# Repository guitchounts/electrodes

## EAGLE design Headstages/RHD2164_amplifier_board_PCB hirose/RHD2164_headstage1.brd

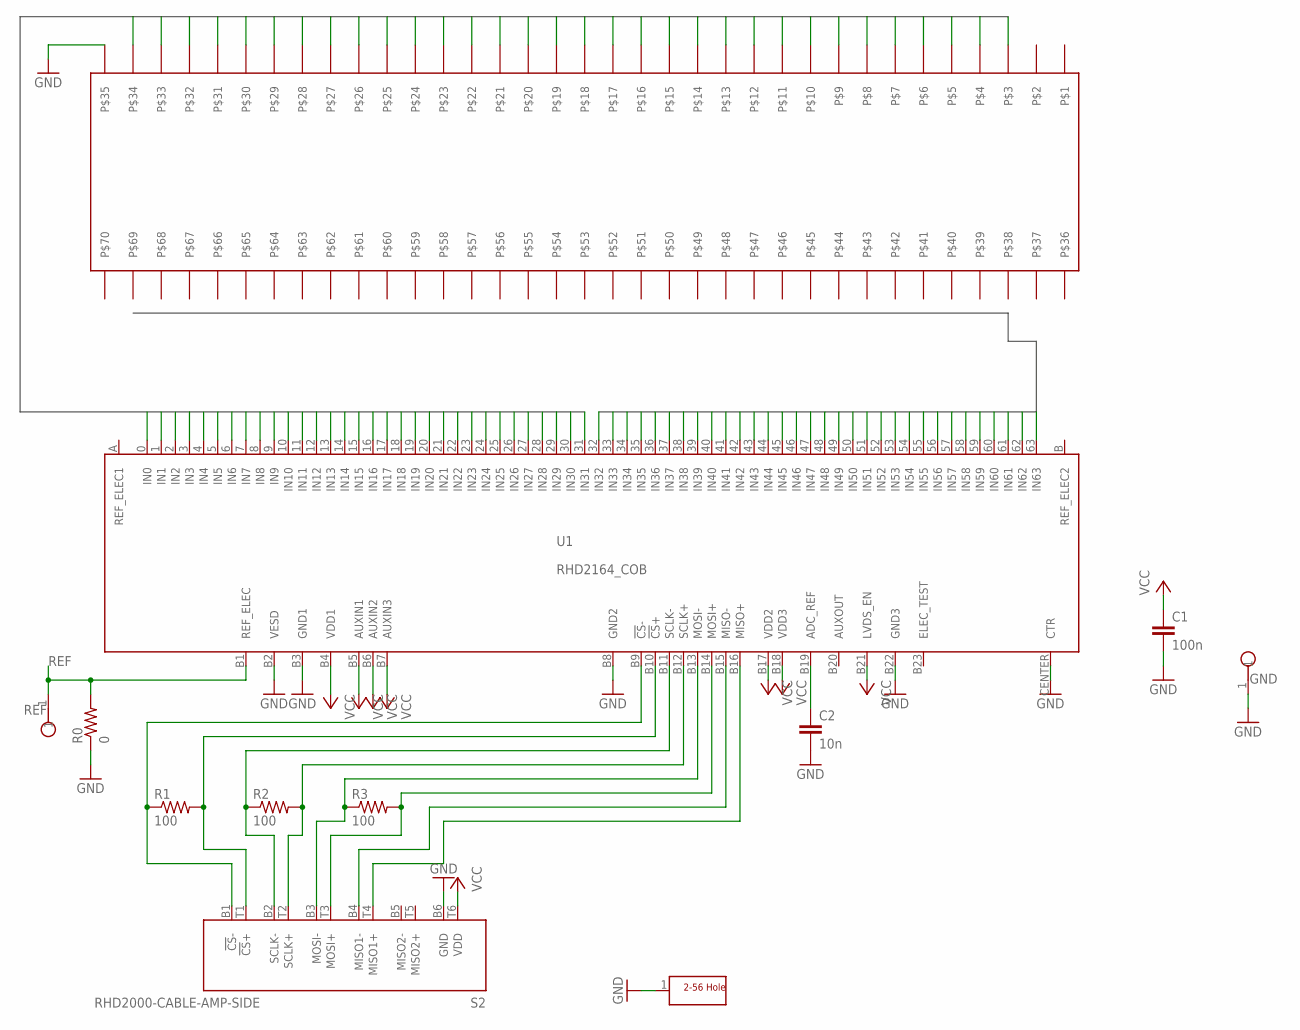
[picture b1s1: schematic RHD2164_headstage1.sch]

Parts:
C1: 100n; 0402
C2: 10n; 0201
GND: TESTPOINT_SMALL
H1: SCREW_HOLE_2-56
R0: 0; 0402
R1, R2, R3: 100; 0201
REF: TESTPOINT_SMALL
S2: RHD2000-CABLE-AMP-SIDE; OMNETICS_PZN-12-AA
U1: RHD2164_COB
U$1: HIROSE_DF40_70PIN; HIROSE_DF40C-70DS

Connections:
A0: U1.0 (IN0), U$1.P$3
A1: U1.1 (IN1), U$1.P$4
A2: U1.2 (IN2), U$1.P$5
A3: U1.3 (IN3), U$1.P$6
A4: U1.4 (IN4), U$1.P$7
A5: U1.5 (IN5), U$1.P$8
A6: U1.6 (IN6), U$1.P$9
A7: U1.7 (IN7), U$1.P$10
A8: U1.8 (IN8), U$1.P$11
A9: U1.9 (IN9), U$1.P$12
A10: U1.10 (IN10), U$1.P$13
A11: U1.11 (IN11), U$1.P$14
A12: U1.12 (IN12), U$1.P$15
A13: U1.13 (IN13), U$1.P$16
A14: U1.14 (IN14), U$1.P$17
A15: U1.15 (IN15), U$1.P$18
A16: U1.16 (IN16), U$1.P$19
A17: U1.17 (IN17), U$1.P$20
A18: U1.18 (IN18), U$1.P$21
A19: U1.19 (IN19), U$1.P$22
A20: U1.20 (IN20), U$1.P$23
A21: U1.21 (IN21), U$1.P$24
A22: U1.22 (IN22), U$1.P$25
A23: U1.23 (IN23), U$1.P$26
A24: U1.24 (IN24), U$1.P$27
A25: U1.25 (IN25), U$1.P$28
A26: U1.26 (IN26), U$1.P$29
A27: U1.27 (IN27), U$1.P$30
A28: U1.28 (IN28), U$1.P$31
A29: U1.29 (IN29), U$1.P$32
A30: U1.30 (IN30), U$1.P$33
A31: U1.31 (IN31), U$1.P$34
B0: U1.32 (IN32)
B1: U1.33 (IN33)
B2: U1.34 (IN34)
B3: U1.35 (IN35)
B4: U1.36 (IN36)
B5: U1.37 (IN37)
B6: U1.38 (IN38)
B7: U1.39 (IN39)
B8: U1.40 (IN40)
B9: U1.41 (IN41)
B10: U1.42 (IN42)
B11: U1.43 (IN43)
B12: U1.44 (IN44)
B13: U1.45 (IN45)
B14: U1.46 (IN46)
B15: U1.47 (IN47)
B16: U1.48 (IN48)
B17: U1.49 (IN49)
B18: U1.50 (IN50)
B19: U1.51 (IN51)
B20: U1.52 (IN52)
B21: U1.53 (IN53)
B22: U1.54 (IN54)
B23: U1.55 (IN55)
B24: U1.56 (IN56)
B25: U1.57 (IN57)
B26: U1.58 (IN58)
B27: U1.59 (IN59)
B28: U1.60 (IN60)
B29: U1.61 (IN61)
B30: U1.62 (IN62)
B31: U1.63 (IN63)
GND: C1.2, C2.2, GND.1, H1.1, R0.1, S2.B6 (GND), U1.B2 (VESD), U1.B3 (GND1), U1.B8 (GND2), U1.B22 (GND3), U1.CENTER (CTR), U$1.P$35
unnamed: S2.T4 (MISO1+), U1.B16 (MISO+)
unnamed: R1.1, S2.B1 (!CS!-), U1.B9 (!CS!-)
unnamed: R1.2, S2.T1 (!CS!+), U1.B10 (!CS!+)
unnamed: R2.1, S2.B2 (SCLK-), U1.B11 (SCLK-)
unnamed: R2.2, S2.T2 (SCLK+), U1.B12 (SCLK+)
unnamed: R3.1, S2.B3 (MOSI-), U1.B13 (MOSI-)
unnamed: R3.2, S2.T3 (MOSI+), U1.B14 (MOSI+)
unnamed: S2.B4 (MISO1-), U1.B15 (MISO-)
unnamed: C2.1, U1.B19 (ADC_REF)
REF: R0.2, REF.1, U1.B1 (REF_ELEC)
VCC: C1.1, S2.T6 (VDD), U1.B4 (VDD1), U1.B5 (AUXIN1), U1.B6 (AUXIN2), U1.B7 (AUXIN3), U1.B17 (VDD2), U1.B18 (VDD3), U1.B21 (LVDS_EN)

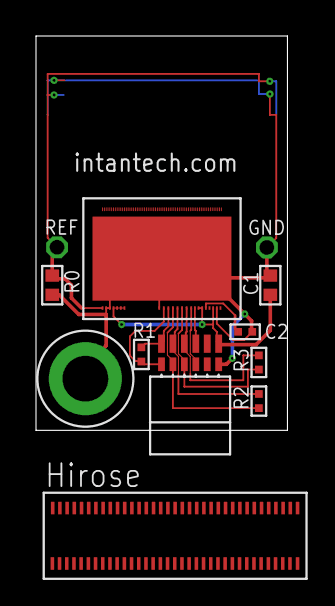
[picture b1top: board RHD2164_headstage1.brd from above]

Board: 2 copper layers, 14.0 x 21.9 mm, 12 parts (0 on the bottom side), 44 nets.

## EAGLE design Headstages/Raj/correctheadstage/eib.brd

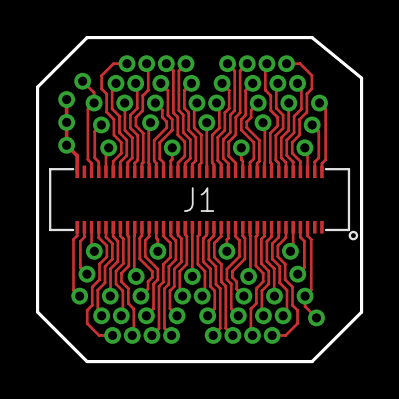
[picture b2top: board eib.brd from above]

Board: 2 copper layers, 18.0 x 18.0 mm, 72 parts (0 on the bottom side), 67 nets.

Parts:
0_0, 0_1, 1_0, 1_1, 2_0, 2_1, 3_0, 3_1, 4_0, 4_1, 5_0, 5_1, 6_0, 6_1, 7_0, 7_1, 8_0, 8_1, 9_0, 9_1, 10_0, 10_1, 11_0, 11_1, 12_0, 12_1, 13_0, 13_1, 14_0, 14_1, 15_0, 15_1, 16_0, 16_1, 17_0, 17_1, 18_0, 18_1, 19_0, 19_1, 20_0, 20_1, 21_0, 21_1, 22_0, 22_1, 23_0, 23_1, 24_0, 24_1, 25_0, 25_1, 26_0, 26_1, 27_0, 27_1, 28_0, 28_1, 29_0, 29_1, 30_0, 30_1, 31_0, 31_1: PAD_20_37
GND, GND1, GND2: PAD_20_37
J1: HIROSE_DF40-70DS; HIROSE_DF40C-70DS
REF_0, REF_0C, REF_1, REF_1C: PAD_20_37

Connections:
unnamed: 0_0.1, J1.4
unnamed: 1_0.1, J1.5
unnamed: 2_0.1, J1.6
unnamed: 3_0.1, J1.7
unnamed: 4_0.1, J1.8
unnamed: 5_0.1, J1.9
unnamed: 6_0.1, J1.10
unnamed: 7_0.1, J1.11
unnamed: 8_0.1, J1.12
unnamed: 9_0.1, J1.13
unnamed: 10_0.1, J1.14
unnamed: 11_0.1, J1.15
unnamed: 12_0.1, J1.16
unnamed: 13_0.1, J1.17
unnamed: 14_0.1, J1.18
unnamed: 15_0.1, J1.19
unnamed: 16_0.1, J1.20
unnamed: 17_0.1, J1.21
unnamed: 18_0.1, J1.22
unnamed: 19_0.1, J1.23
unnamed: 20_0.1, J1.24
unnamed: 21_0.1, J1.25
unnamed: 22_0.1, J1.26
unnamed: 23_0.1, J1.27
unnamed: 24_0.1, J1.28
unnamed: 25_0.1, J1.29
unnamed: 26_0.1, J1.30
unnamed: 27_0.1, J1.31
unnamed: 28_0.1, J1.32
unnamed: 29_0.1, J1.33
unnamed: 30_0.1, J1.34
unnamed: 31_0.1, J1.35
unnamed: 0_1.1, J1.39
unnamed: 1_1.1, J1.40
unnamed: 2_1.1, J1.41
unnamed: 3_1.1, J1.42
unnamed: 4_1.1, J1.43
unnamed: 5_1.1, J1.44
unnamed: 6_1.1, J1.45
unnamed: 7_1.1, J1.46
unnamed: 8_1.1, J1.47
unnamed: 9_1.1, J1.48
unnamed: 10_1.1, J1.49
unnamed: 11_1.1, J1.50
unnamed: 12_1.1, J1.51
unnamed: 13_1.1, J1.52
unnamed: 14_1.1, J1.53
unnamed: 15_1.1, J1.54
unnamed: 16_1.1, J1.55
unnamed: 17_1.1, J1.56
unnamed: 18_1.1, J1.57
unnamed: 19_1.1, J1.58
unnamed: 20_1.1, J1.59
unnamed: 21_1.1, J1.60
unnamed: 22_1.1, J1.61
unnamed: 23_1.1, J1.62
unnamed: 24_1.1, J1.63
unnamed: 25_1.1, J1.64
unnamed: 26_1.1, J1.65
unnamed: 27_1.1, J1.66
unnamed: 28_1.1, J1.67
unnamed: 29_1.1, J1.68
unnamed: 30_1.1, J1.69
unnamed: 31_1.1, J1.70
unnamed: J1.3, REF_0.1, REF_0C.1
unnamed: J1.38, REF_1.1, REF_1C.1
unnamed: GND.1, GND1.1, GND2.1, J1.36

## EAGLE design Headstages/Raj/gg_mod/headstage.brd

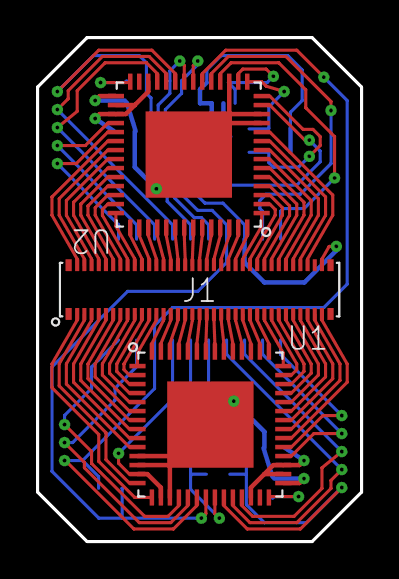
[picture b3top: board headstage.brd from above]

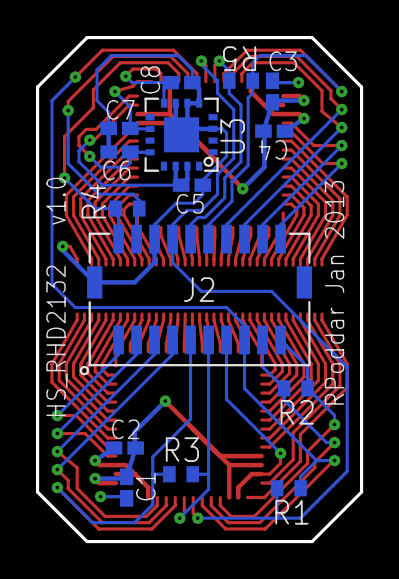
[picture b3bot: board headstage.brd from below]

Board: 4 copper layers, 18.0 x 28.0 mm, 18 parts (15 on the bottom side), 93 nets.

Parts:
C1, C3: 10nF; C0402K
C2, C4, C5, C6, C7, C8: 100nF; C0402K
J1: HIROSE_DF40-70DP; HIROSE_DF40C-70DP
J2: MOLEX_501190-2017
R1, R2, R3, R4, R5: 100; R0402
U1, U2: RHD2132_QFN; QFN56_8_X_8_LARGE
U3: ADXL335

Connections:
CS+_0: J2.17, R2.1, U1.19
CS+_1: J2.4, R4.1, U2.19
CS-_0: J2.19, R2.2, U1.18
CS-_1: J2.2, R4.2, U2.18
ELEC_TEST_0: J2.1, U1.33
ELEC_TEST_1: J2.20, U2.33
GND: C1.2, C2.2, C3.2, C4.2, C5.2, C6.1, C7.1, C8.1, J1.36, J2.6, J2.NC1, U1.11, U1.12, U1.17, U1.29, U1.CENTER, U2.11, U2.12, U2.17, U2.29, U2.CENTER, U3.COM1, U3.COM2, U3.COM3, U3.COM4, U3.CTR
IN0_0: J1.4, U1.9
IN0_1: J1.39, U2.9
IN1_0: J1.5, U1.8
IN1_1: J1.40, U2.8
IN2_0: J1.6, U1.7
IN2_1: J1.41, U2.7
IN3_0: J1.7, U1.6
IN3_1: J1.42, U2.6
IN4_0: J1.8, U1.5
IN4_1: J1.43, U2.5
IN5_0: J1.9, U1.4
IN5_1: J1.44, U2.4
IN6_0: J1.10, U1.3
IN6_1: J1.45, U2.3
IN7_0: J1.11, U1.2
IN7_1: J1.46, U2.2
IN8_0: J1.12, U1.1
IN8_1: J1.47, U2.1
IN9_0: J1.13, U1.56
IN9_1: J1.48, U2.56
IN10_0: J1.14, U1.55
IN10_1: J1.49, U2.55
IN11_0: J1.15, U1.54
IN11_1: J1.50, U2.54
IN12_0: J1.16, U1.53
IN12_1: J1.51, U2.53
IN13_0: J1.17, U1.52
IN13_1: J1.52, U2.52
IN14_0: J1.18, U1.51
IN14_1: J1.53, U2.51
IN15_0: J1.19, U1.50
IN15_1: J1.54, U2.50
IN16_0: J1.20, U1.49
IN16_1: J1.55, U2.49
IN17_0: J1.21, U1.48
IN17_1: J1.56, U2.48
IN18_0: J1.22, U1.47
IN18_1: J1.57, U2.47
IN19_0: J1.23, U1.46
IN19_1: J1.58, U2.46
IN20_0: J1.24, U1.45
IN20_1: J1.59, U2.45
IN21_0: J1.25, U1.44
IN21_1: J1.60, U2.44
IN22_0: J1.26, U1.43
IN22_1: J1.61, U2.43
IN23_0: J1.27, U1.42
IN23_1: J1.62, U2.42
IN24_0: J1.28, U1.41
IN24_1: J1.63, U2.41
IN25_0: J1.29, U1.40
IN25_1: J1.64, U2.40
IN26_0: J1.30, U1.39
IN26_1: J1.65, U2.39
IN27_0: J1.31, U1.38
IN27_1: J1.66, U2.38
IN28_0: J1.32, U1.37
IN28_1: J1.67, U2.37
IN29_0: J1.33, U1.36
IN29_1: J1.68, U2.36
IN30_0: J1.34, U1.35
IN30_1: J1.69, U2.35
IN31_0: J1.35, U1.34
IN31_1: J1.70, U2.34
MISO+_0: J2.5, U1.25
MISO+_1: J2.16, U2.25
MISO-_0: J2.7, U1.24
MISO-_1: J2.14, U2.24
MOSI+_0: J2.9, R3.1, U1.23
MOSI+_1: J2.12, R5.1, U2.23
MOSI-_0: J2.11, R3.2, U1.22
MOSI-_1: J2.10, R5.2, U2.22
unnamed: J1.1, U1.15
unnamed: J1.2, U1.14
unnamed: C1.1, U1.28
unnamed: C3.1, U2.28
REF_ELEC_0: J1.3, U1.10
REF_ELEC_1: J1.38, U2.10
SCLK+: J2.8, R1.1, U1.21, U2.21
SCLK-: J2.15, R1.2, U1.20, U2.20
VDD: C2.1, C4.1, C5.1, J2.13, U1.13, U1.16, U1.26, U1.30, U1.31, U2.13, U2.26, U2.30, U2.31, U3.VS1, U3.VS2
VESD_0: J2.3, U1.32
VESD_1: J2.18, U2.32
XOUT: C6.2, U2.14, U3.XOUT
YOUT: C7.2, U2.15, U3.YOUT
ZOUT: C8.2, U2.16, U3.ZOUT
